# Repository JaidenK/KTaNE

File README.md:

# KTaNE
Keep Talking and Nobody Explodes

# Build Instructions
1. Arduino IDE version 2.2.1
2. Clear out your Arduino libraries folder.
    - ex: "C:\Users\kingj\OneDrive\Documents\Arduino\libraries\" should exist and be empty
3. Copy the contents of the repo's libraries folder into your Arduino install's libraries folder, excluding libraries that do not apply to the desired module.
    - ex: For compiling the Sketchpad module, you would copy ES_Framework, KTaNE, and KTaNE_Sketchpad but NOT KTaNE_Timer or other Module folders
4. Select "Arduino Uno" in the Aruino IDE's board selection menu

The code should now build.

# Programming Instructions
0. Refer to https://docs.arduino.cc/built-in-examples/arduino-isp/ArduinoToBreadboard/
    - See also: https://www.instructables.com/Configure-Arduino-IDE-for-Atmega-328P-to-Use-8MHz-/
    - See also: https://www.youtube.com/watch?v=dcLeKj00t_I
1. Get an Aruino Uno R3 and upload the "ArduinoISP" example sketch to it.
3. Connect the 6-pin ISP header on the Arduino to the 6-pin ISP header on the Module, with the exception of the RESET pin.
4. Connect pin 10 on the Arduino to the Reset pin of the Module's ISP header.
    - Pin 10 is the Arduino's default Slave Select pin for the ArduinoISP sketch.
5. Set the Arduino IDE's programmer to "Arduino as ISP" and select "ATMega328P on a breadboard (8 MHz internal clock)" for the board
6. Use "Sketch > Upload Using Programmer" menu command to upload the code

# Documentation
Communication Protocols:
https://docs.google.com/document/d/1BFYc2orsP6i7TOAGHv1l20GYD-Ui4hXYQUHcmJRFHF8/edit?usp=sharing

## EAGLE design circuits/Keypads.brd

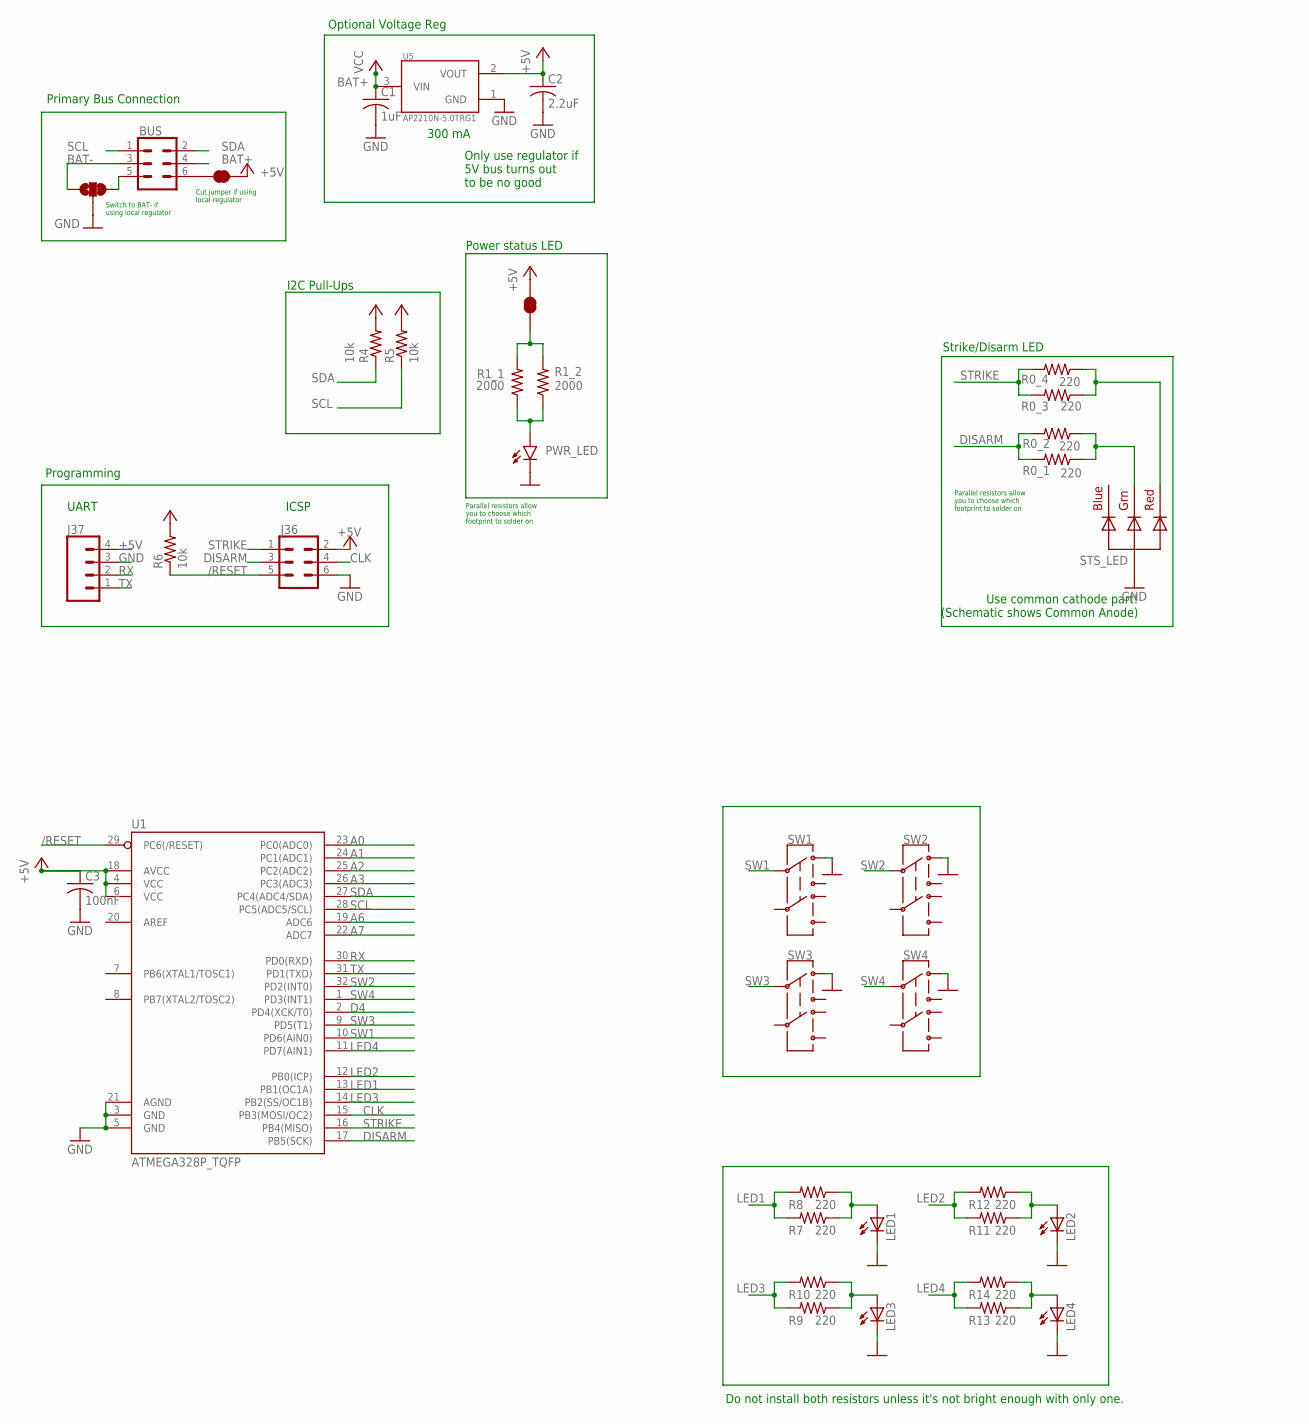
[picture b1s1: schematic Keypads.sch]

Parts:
BUS: CONN_03X2SHROUD; 2X3-SHROUDED
C1: 1uF; C0805
C2: 2.2uF; C0805
C3: 100nF; C0805
J36: CONN_03X22X3_SILK_MALE_PTH; 2X3
J37: CONN_04; 1X04
JP1, JP3: JUMPER-SMT_2_NC_TRACE_SILK; SMT-JUMPER_2_NC_TRACE_SILK
JP2: JUMPER-SMT_3_1-NC_TRACE_SILK; SMT-JUMPER_3_1-NC_TRACE_SILK
LED1, LED2, LED3, LED4: LEDCHIP-LED0603; CHIP-LED0603
PWR_LED: LED3MM; LED_3MM
R0_1, R0_3: 220; 0204/7
R0_2, R0_4, R7, R8, R9, R10, R11, R12, R13, R14: 220; R0805
R1_1: 2000; 0204/7
R1_2: 2000; R0805
R4, R5, R6: 10k; 0204/7
STS_LED: RGBLED_CA-5MM; LED5MMRGB
SW1, SW2, SW3, SW4: MHPS2283N-SWITCH-PUSH-DPDT; MHPS2283N
U1: ATMEGA328P_TQFP; TQFP32-08
U5: AP2210N-5.0TRG1; SOT95P280X145-3N

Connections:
+5V: C2.1, C3.1, J36.2, J37.4, JP1.2, JP3.2, R4.2, R5.2, R6.2, U1.4 (VCC), U1.6 (VCC), U1.18 (AVCC), U5.2 (VOUT)
/RESET: J36.5, R6.1, U1.29 (PC6(/RESET))
A0: U1.23 (PC0(ADC0))
A1: U1.24 (PC1(ADC1))
A2: U1.25 (PC2(ADC2))
A3: U1.26 (PC3(ADC3))
A6: U1.19 (ADC6)
A7: U1.22 (ADC7)
BAT+: BUS.4, C1.1, U5.3 (VIN)
BAT-: BUS.3, JP2.1
CLK: J36.4, U1.15 (PB3(MOSI/OC2))
CONN_5V: BUS.6, JP1.1
CONN_GND: BUS.5, JP2.3
D4: U1.2 (PD4(XCK/T0))
DISARM: J36.3, R0_1.2, R0_2.2, U1.17 (PB5(SCK))
GND: C1.2, C2.2, C3.2, J36.6, J37.3, JP2.2, LED1.C, LED2.C, LED3.C, LED4.C, PWR_LED.K (C), STS_LED.2 (VCC), SW1.P$1 (1), SW2.P$1 (1), SW3.P$1 (1), SW4.P$1 (1), U1.3 (GND), U1.5 (GND), U1.21 (AGND), U5.1 (GND)
LED1: R7.2, R8.2, U1.13 (PB1(OC1A))
LED2: R11.2, R12.2, U1.12 (PB0(ICP))
LED3: R9.2, R10.2, U1.14 (PB2(SS/OC1B))
LED4: R13.2, R14.2, U1.11 (PD7(AIN1))
unnamed: PWR_LED.A, R1_1.1, R1_2.1
unnamed: JP3.1, R1_1.2, R1_2.2
unnamed: LED3.A, R9.1, R10.1
unnamed: LED1.A, R7.1, R8.1
unnamed: LED2.A, R11.1, R12.1
unnamed: LED4.A, R13.1, R14.1
unnamed: R0_1.1, R0_2.1, STS_LED.3 (GREEN)
unnamed: R0_3.1, R0_4.1, STS_LED.1 (RED)
RX: J37.2, U1.30 (PD0(RXD))
SCL: BUS.1, R5.1, U1.28 (PC5(ADC5/SCL))
SDA: BUS.2, R4.1, U1.27 (PC4(ADC4/SDA))
STRIKE: J36.1, R0_3.2, R0_4.2, U1.16 (PB4(MISO))
SW1: SW1.P$2 (2), U1.10 (PD6(AIN0))
SW2: SW2.P$2 (2), U1.32 (PD2(INT0))
SW3: SW3.P$2 (2), U1.9 (PD5(T1))
SW4: SW4.P$2 (2), U1.1 (PD3(INT1))
TX: J37.1, U1.31 (PD1(TXD))

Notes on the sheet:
Only use regulator if 5V bus turns out to be no good
300 mA
Cut jumper if using local regulator
Use common cathode part! (Schematic shows Common Anode)
Switch to BAT- if using local regulator
Power status LED
ICSP
UART
I2C Pull-Ups
Primary Bus Connection
Optional Voltage Reg
Strike/Disarm LED
Programming
Do not install both resistors unless it's not bright enough with only one.
Parallel resistors allow you to choose which footprint to solder on

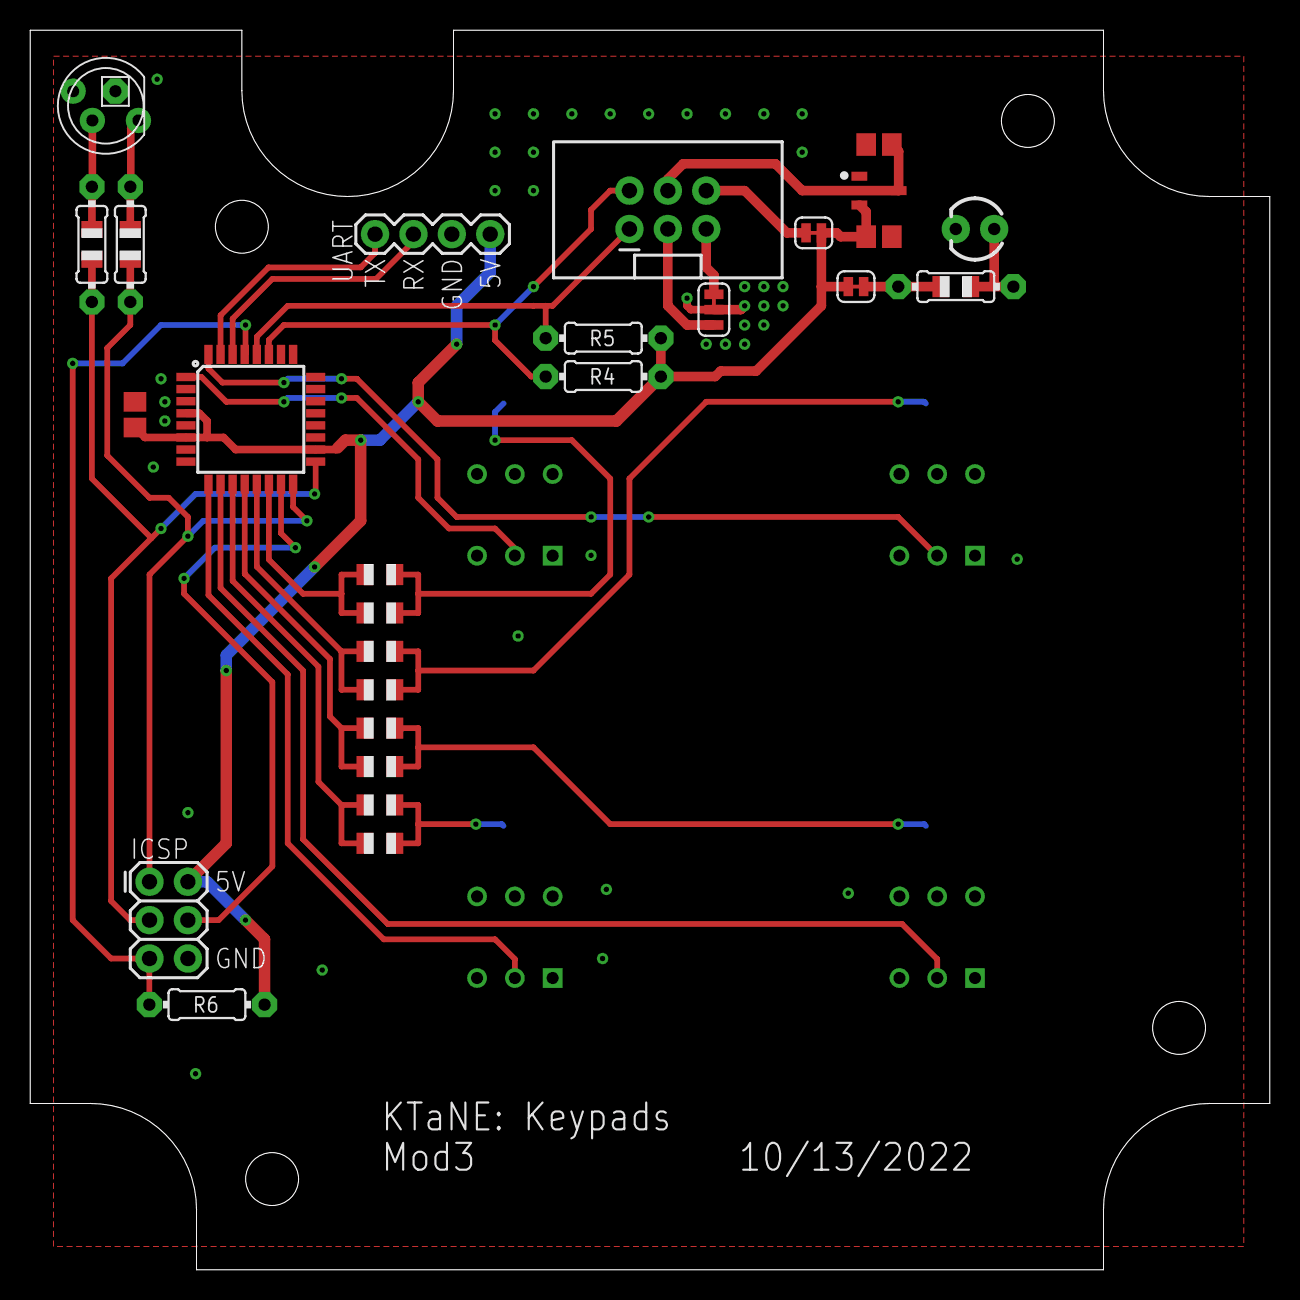
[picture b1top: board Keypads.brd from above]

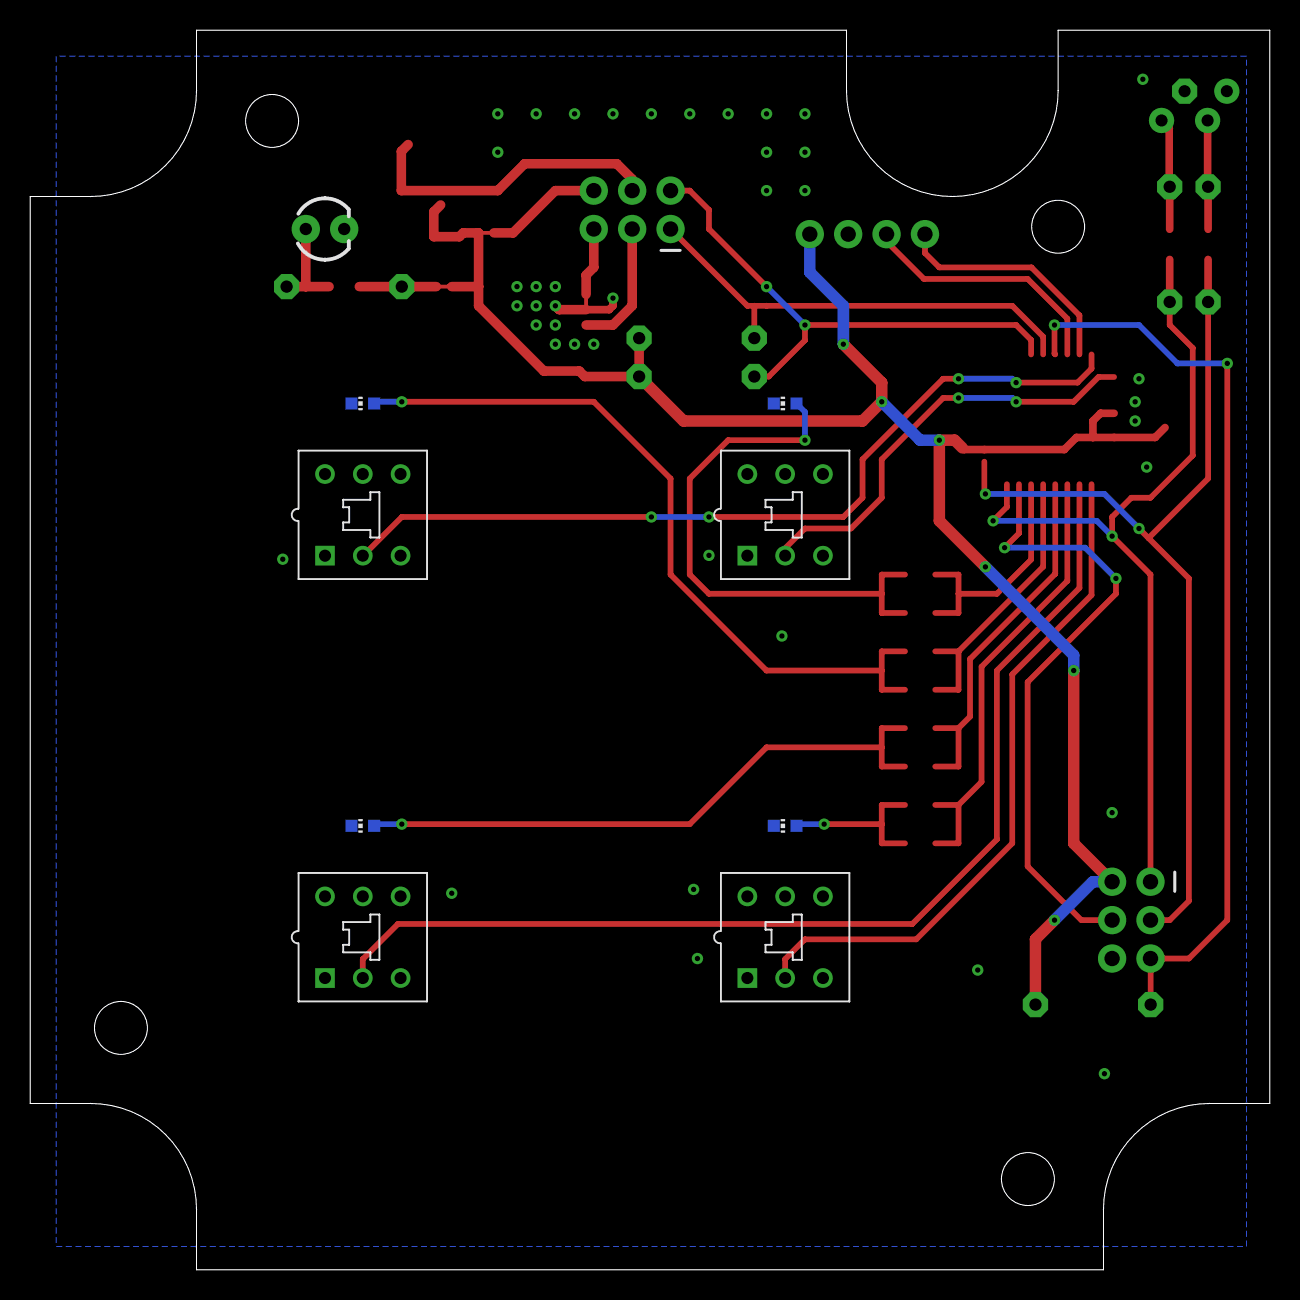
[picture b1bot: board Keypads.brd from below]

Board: 2 copper layers, 82.0 x 82.0 mm, 38 parts (8 on the bottom side), 30 nets.

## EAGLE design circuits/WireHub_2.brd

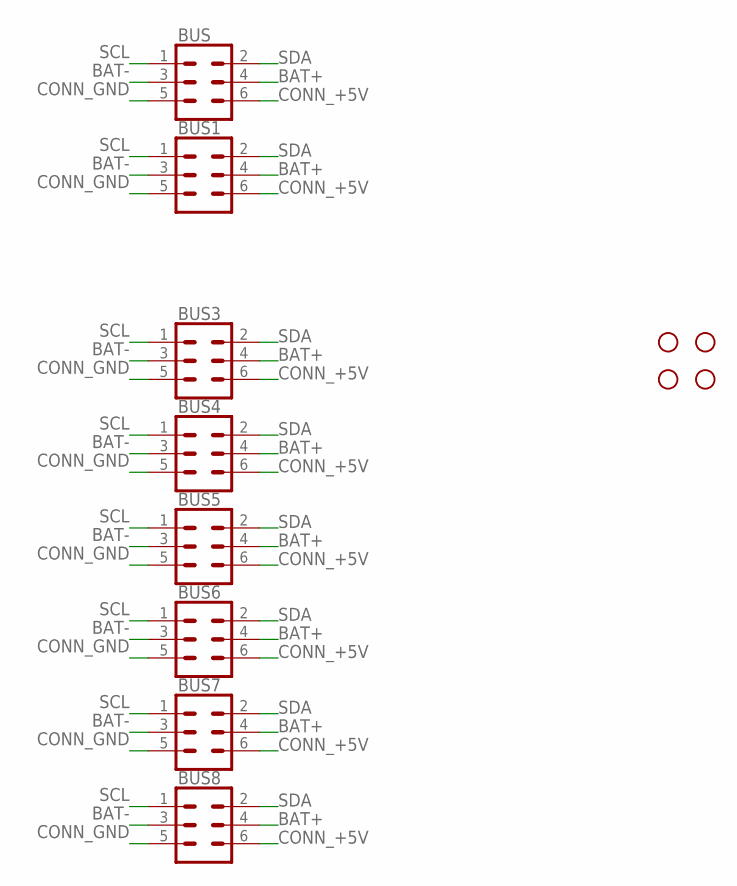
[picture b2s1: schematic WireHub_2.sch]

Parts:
BUS, BUS1, BUS3, BUS4, BUS5, BUS6, BUS7, BUS8: CONN_03X2SHROUD; 2X3-SHROUDED
H1, H2, H3, H4: STAND-OFF

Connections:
BAT+: BUS.4, BUS1.4, BUS3.4, BUS4.4, BUS5.4, BUS6.4, BUS7.4, BUS8.4
BAT-: BUS.3, BUS1.3, BUS3.3, BUS4.3, BUS5.3, BUS6.3, BUS7.3, BUS8.3
CONN_+5V: BUS.6, BUS1.6, BUS3.6, BUS4.6, BUS5.6, BUS6.6, BUS7.6, BUS8.6
CONN_GND: BUS.5, BUS1.5, BUS3.5, BUS4.5, BUS5.5, BUS6.5, BUS7.5, BUS8.5
SCL: BUS.1, BUS1.1, BUS3.1, BUS4.1, BUS5.1, BUS6.1, BUS7.1, BUS8.1
SDA: BUS.2, BUS1.2, BUS3.2, BUS4.2, BUS5.2, BUS6.2, BUS7.2, BUS8.2

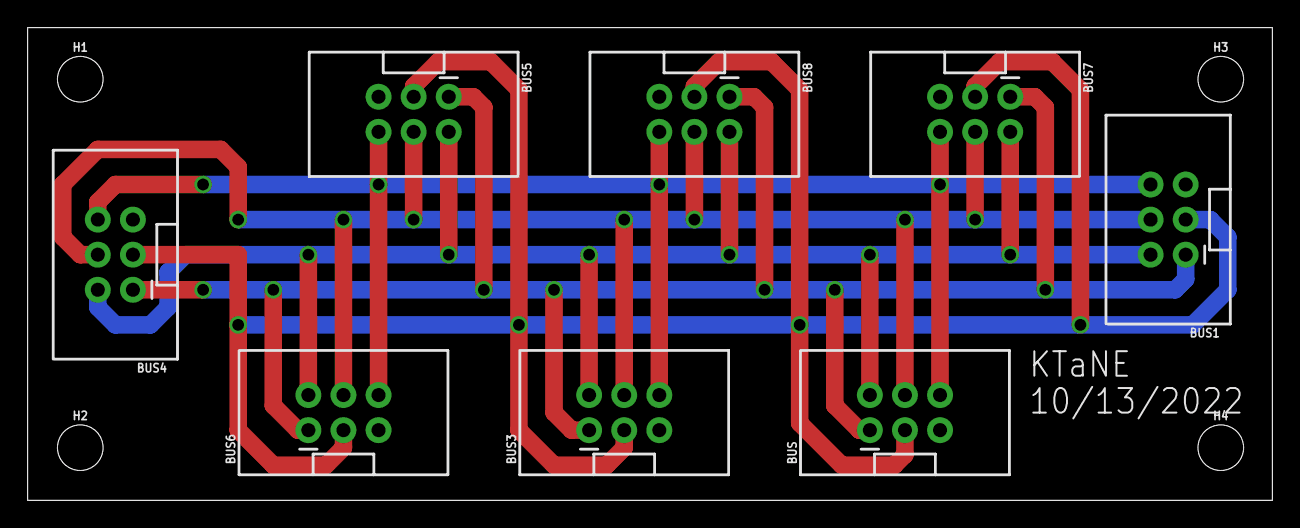
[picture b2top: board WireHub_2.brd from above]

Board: 2 copper layers, 90.1 x 34.2 mm, 12 parts (0 on the bottom side), 6 nets.

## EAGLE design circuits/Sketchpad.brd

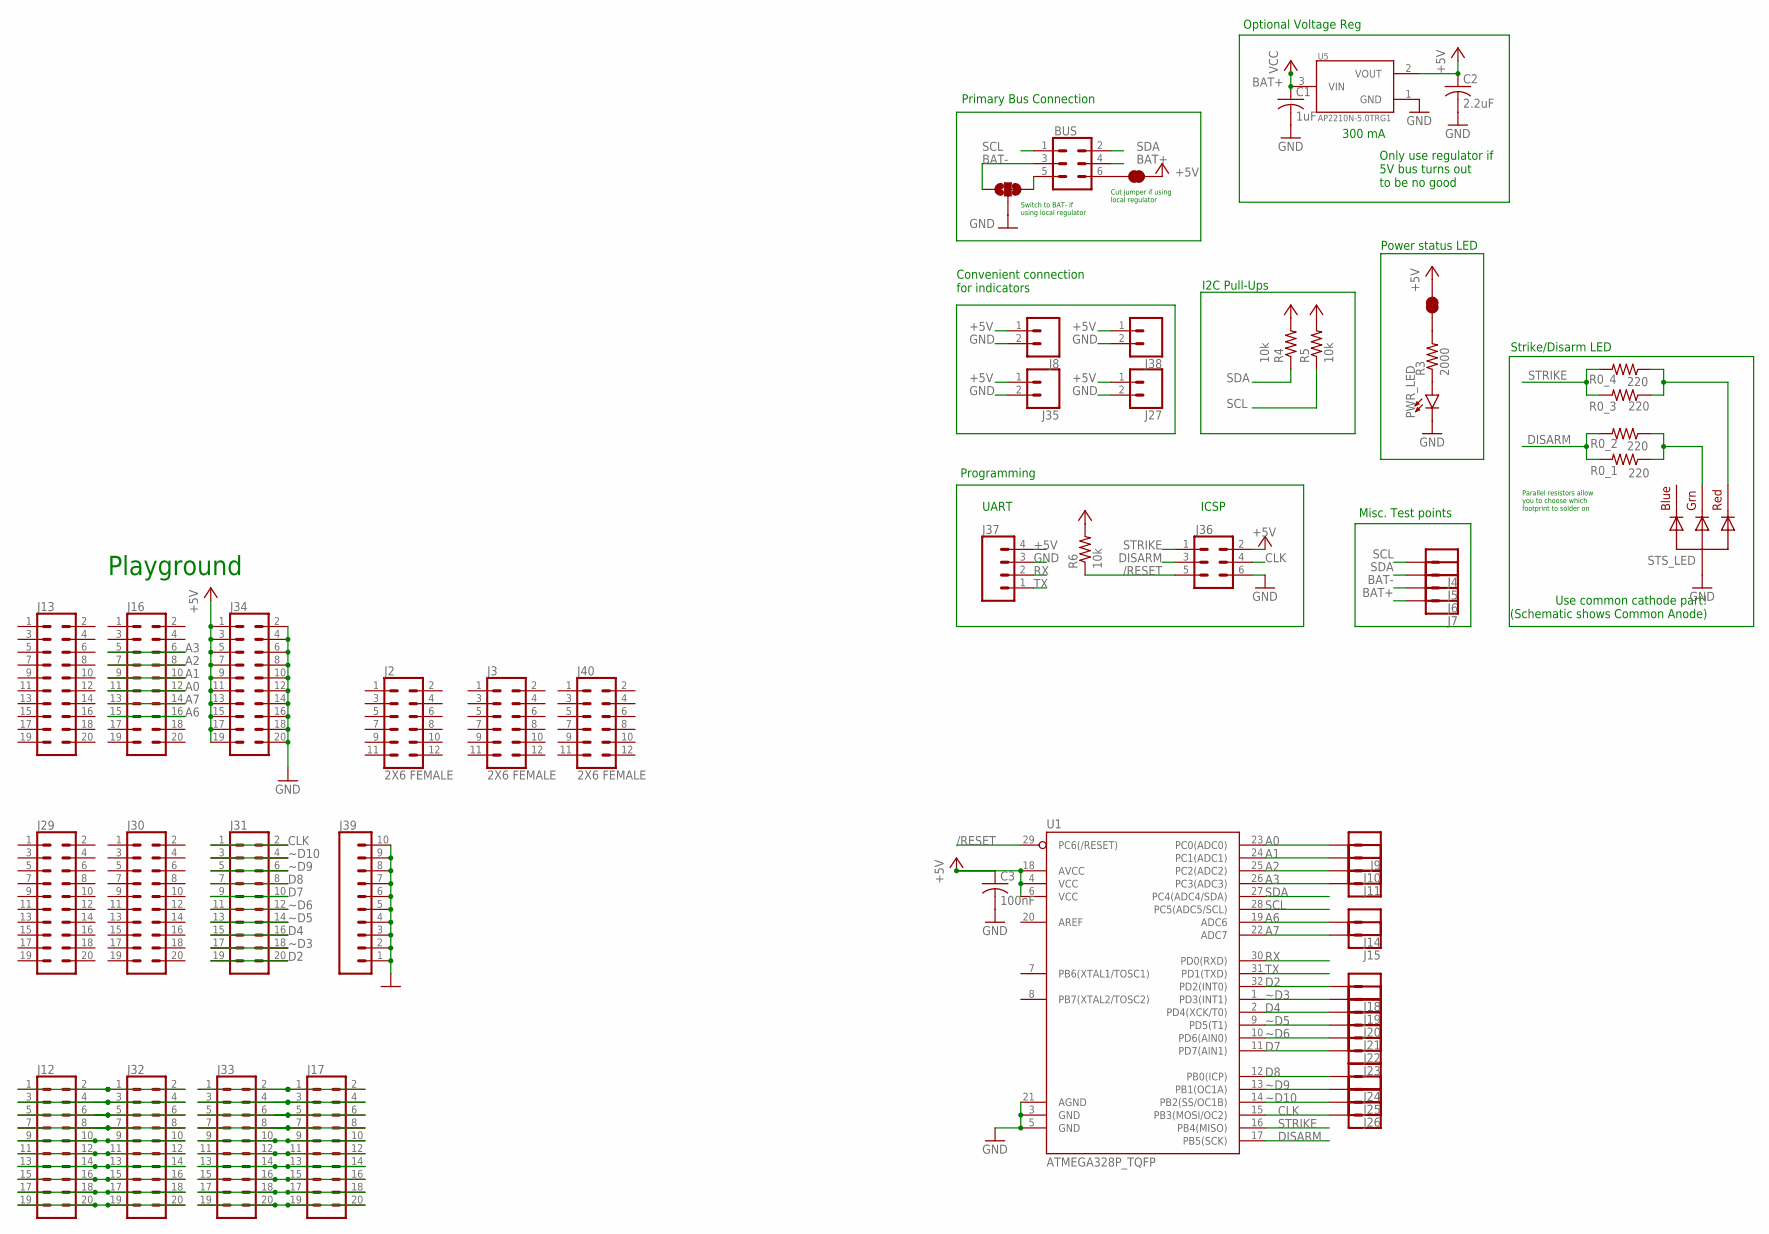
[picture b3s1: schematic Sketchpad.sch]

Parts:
BUS: CONN_03X2SHROUD; 2X3-SHROUDED
C1: 1uF; C0805
C2: 2.2uF; C0805
C3: 100nF; C0805
J1, J4, J5, J6, J7, J9, J10, J11, J14, J15, J18, J19, J20, J21, J22, J23, J24, J25, J26, J28: CONN_01; 1X01
J2, J3, J40: 2X6 FEMALE; 2X6
J8, J27, J35, J38: CONN_02POLAR; MOLEX-1X2
J12, J13, J16, J17, J29, J30, J31, J32, J33, J34: CONN_10X2NOSILK; 2X10_NOSILK
J36: CONN_03X22X3_SILK_MALE_PTH; 2X3
J37: CONN_04; 1X04
J39: CONN_10NO_SILK_PTH_FEMALE; 1X10_NO_SILK
JP1, JP3: JUMPER-SMT_2_NC_TRACE_SILK; SMT-JUMPER_2_NC_TRACE_SILK
JP2: JUMPER-SMT_3_1-NC_TRACE_SILK; SMT-JUMPER_3_1-NC_TRACE_SILK
PWR_LED: LED3MM; LED_3MM
R0_1, R0_3: 220; 0204/7
R0_2, R0_4: 220; R0805
R3: 2000; 0204/7
R4, R5, R6: 10k; 0204/7
STS_LED: RGBLED_CA-5MM; LED5MMRGB
U1: ATMEGA328P_TQFP; TQFP32-08
U5: AP2210N-5.0TRG1; SOT95P280X145-3N

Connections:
+5V: C2.1, C3.1, J8.1, J27.1, J34.1, J34.3, J34.5, J34.7, J34.9, J34.11, J34.13, J34.15, J34.17, J34.19, J35.1, J36.2, J37.4, J38.1, JP1.2, JP3.2, R4.2, R5.2, R6.2, U1.4 (VCC), U1.6 (VCC), U1.18 (AVCC), U5.2 (VOUT)
/RESET: J36.5, R6.1, U1.29 (PC6(/RESET))
A0: J9.1, J16.11, J16.12, U1.23 (PC0(ADC0))
A1: J10.1, J16.9, J16.10, U1.24 (PC1(ADC1))
A2: J11.1, J16.7, J16.8, U1.25 (PC2(ADC2))
A3: J16.5, J16.6, J28.1, U1.26 (PC3(ADC3))
A6: J14.1, J16.15, J16.16, U1.19 (ADC6)
A7: J15.1, J16.13, J16.14, U1.22 (ADC7)
BAT+: BUS.4, C1.1, J7.1, U5.3 (VIN)
BAT-: BUS.3, J6.1, JP2.1
CLK: J1.1, J31.1, J31.2, J36.4, U1.15 (PB3(MOSI/OC2))
CONN_5V: BUS.6, JP1.1
CONN_GND: BUS.5, JP2.3
D2: J18.1, J31.19, J31.20, U1.32 (PD2(INT0))
D4: J20.1, J31.15, J31.16, U1.2 (PD4(XCK/T0))
D7: J23.1, J31.9, J31.10, U1.11 (PD7(AIN1))
D8: J24.1, J31.7, J31.8, U1.12 (PB0(ICP))
DISARM: J36.3, R0_1.2, R0_2.2, U1.17 (PB5(SCK))
GND: C1.2, C2.2, C3.2, J8.2, J27.2, J34.2, J34.4, J34.6, J34.8, J34.10, J34.12, J34.14, J34.16, J34.18, J34.20, J35.2, J36.6, J37.3, J38.2, J39.1, J39.2, J39.3, J39.4, J39.5, J39.6, J39.7, J39.8, J39.9, J39.10, JP2.2, PWR_LED.K (C), STS_LED.2 (VCC), U1.3 (GND), U1.5 (GND), U1.21 (AGND), U5.1 (GND)
unnamed: R0_1.1, R0_2.1, STS_LED.3 (GREEN)
unnamed: R0_3.1, R0_4.1, STS_LED.1 (RED)
unnamed: J12.1, J12.2, J32.1, J32.2
unnamed: J12.3, J12.4, J32.3, J32.4
unnamed: J12.5, J12.6, J32.5, J32.6
unnamed: J12.7, J12.8, J32.7, J32.8
unnamed: J12.9, J12.10, J32.9, J32.10
unnamed: J12.11, J12.12, J32.11, J32.12
unnamed: J12.13, J12.14, J32.13, J32.14
unnamed: J12.15, J12.16, J32.15, J32.16
unnamed: J12.17, J12.18, J32.17, J32.18
unnamed: J12.19, J12.20, J32.19, J32.20
unnamed: J17.1, J17.2, J33.1, J33.2
unnamed: J17.3, J17.4, J33.3, J33.4
unnamed: J17.5, J17.6, J33.5, J33.6
unnamed: J17.7, J17.8, J33.7, J33.8
unnamed: J17.9, J17.10, J33.9, J33.10
unnamed: J17.11, J17.12, J33.11, J33.12
unnamed: J17.13, J17.14, J33.13, J33.14
unnamed: J17.15, J17.16, J33.15, J33.16
unnamed: J17.17, J17.18, J33.17, J33.18
unnamed: J17.19, J17.20, J33.19, J33.20
unnamed: JP3.1, R3.2
unnamed: PWR_LED.A, R3.1
RX: J37.2, U1.30 (PD0(RXD))
SCL: BUS.1, J4.1, R5.1, U1.28 (PC5(ADC5/SCL))
SDA: BUS.2, J5.1, R4.1, U1.27 (PC4(ADC4/SDA))
STRIKE: J36.1, R0_3.2, R0_4.2, U1.16 (PB4(MISO))
TX: J37.1, U1.31 (PD1(TXD))
~D3: J19.1, J31.17, J31.18, U1.1 (PD3(INT1))
~D5: J21.1, J31.13, J31.14, U1.9 (PD5(T1))
~D6: J22.1, J31.11, J31.12, U1.10 (PD6(AIN0))
~D9: J25.1, J31.5, J31.6, U1.13 (PB1(OC1A))
~D10: J26.1, J31.3, J31.4, U1.14 (PB2(SS/OC1B))

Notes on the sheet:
Only use regulator if 5V bus turns out to be no good
300 mA
Cut jumper if using local regulator
Use common cathode part! (Schematic shows Common Anode)
Switch to BAT- if using local regulator
Playground
Misc. Test points
Convenient connection for indicators
Power status LED
ICSP
UART
I2C Pull-Ups
Primary Bus Connection
Optional Voltage Reg
Strike/Disarm LED
Programming
Parallel resistors allow you to choose which footprint to solder on

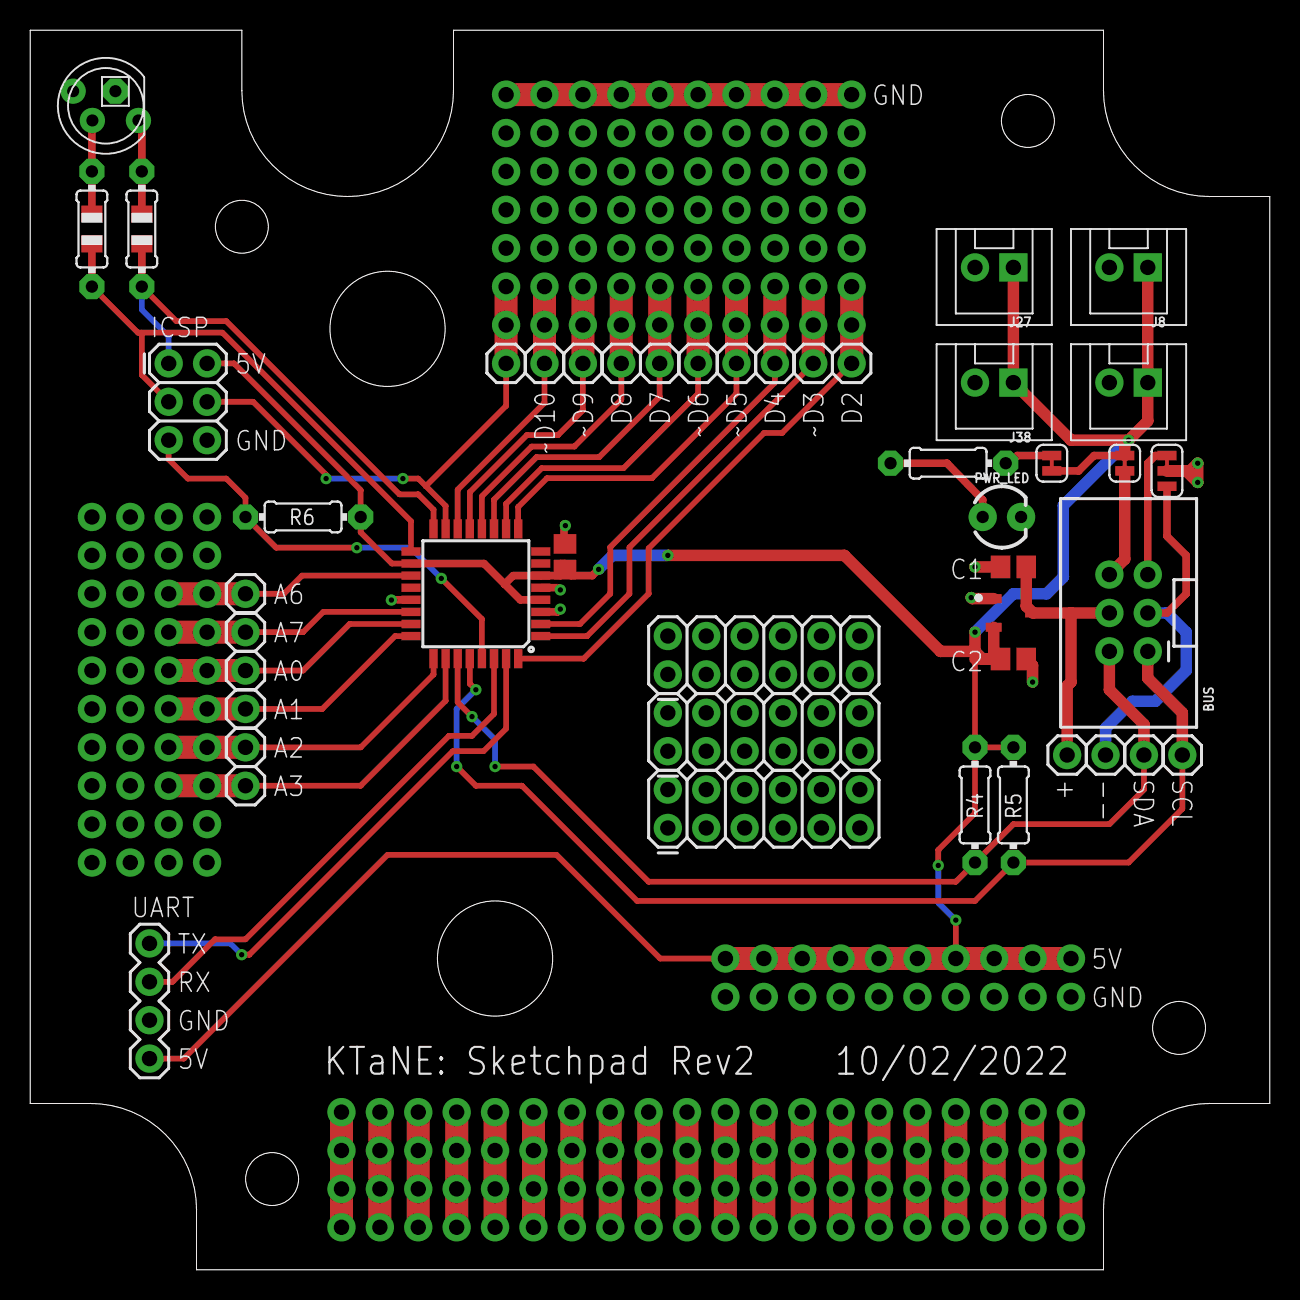
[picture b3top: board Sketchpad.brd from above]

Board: 2 copper layers, 82.0 x 82.0 mm, 59 parts (0 on the bottom side), 53 nets.

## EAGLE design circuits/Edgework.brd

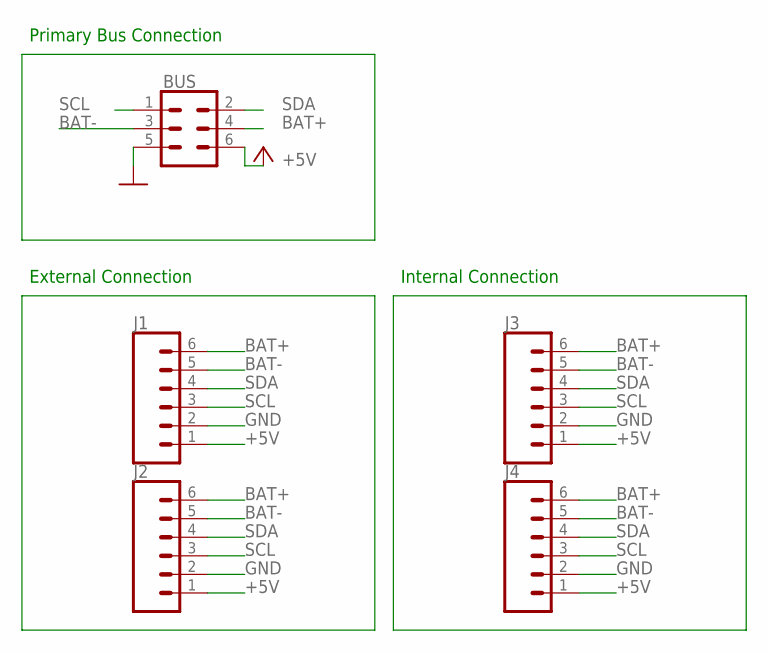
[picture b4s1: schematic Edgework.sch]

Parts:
BUS: CONN_03X2SHROUD; 2X3-SHROUDED
J1, J2, J3, J4: CONN_06NO_SILK_FEMALE_PTH; 1X06_NO_SILK

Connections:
+5V: BUS.6, J1.1, J2.1, J3.1, J4.1
BAT+: BUS.4, J1.6, J2.6, J3.6, J4.6
BAT-: BUS.3, J1.5, J2.5, J3.5, J4.5
GND: BUS.5, J1.2, J2.2, J3.2, J4.2
SCL: BUS.1, J1.3, J2.3, J3.3, J4.3
SDA: BUS.2, J1.4, J2.4, J3.4, J4.4

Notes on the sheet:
Primary Bus Connection
External Connection
Internal Connection

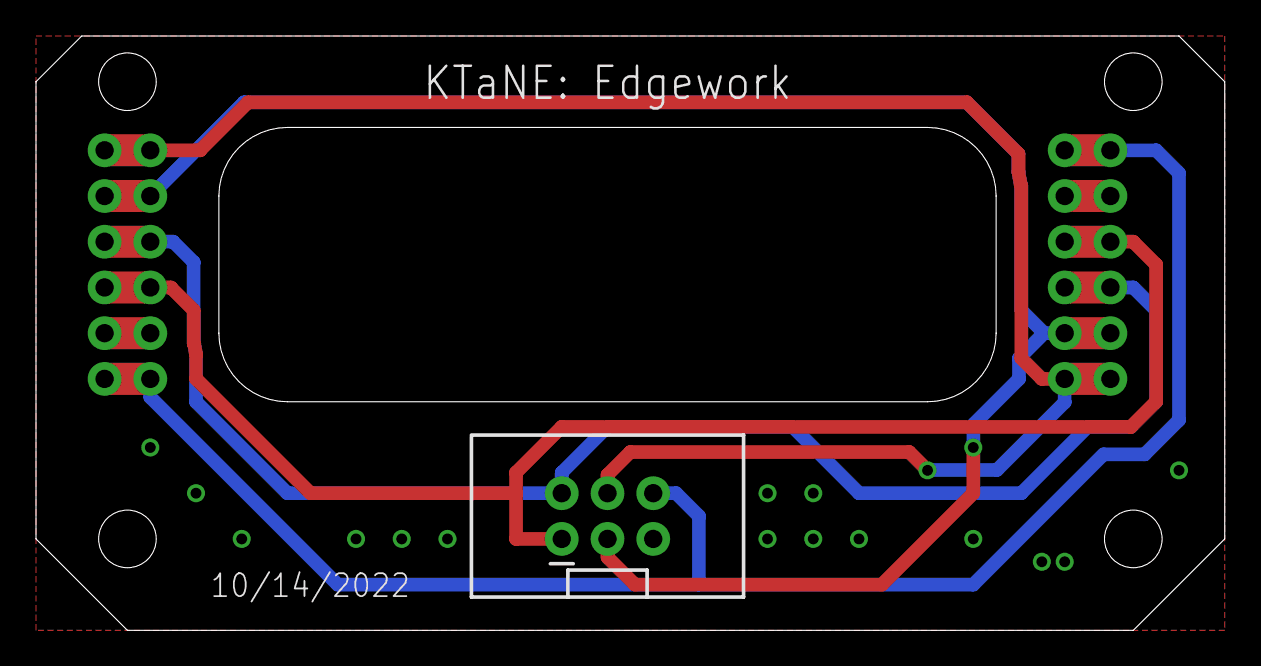
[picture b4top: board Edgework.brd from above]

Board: 2 copper layers, 66.0 x 33.0 mm, 5 parts (0 on the bottom side), 6 nets.

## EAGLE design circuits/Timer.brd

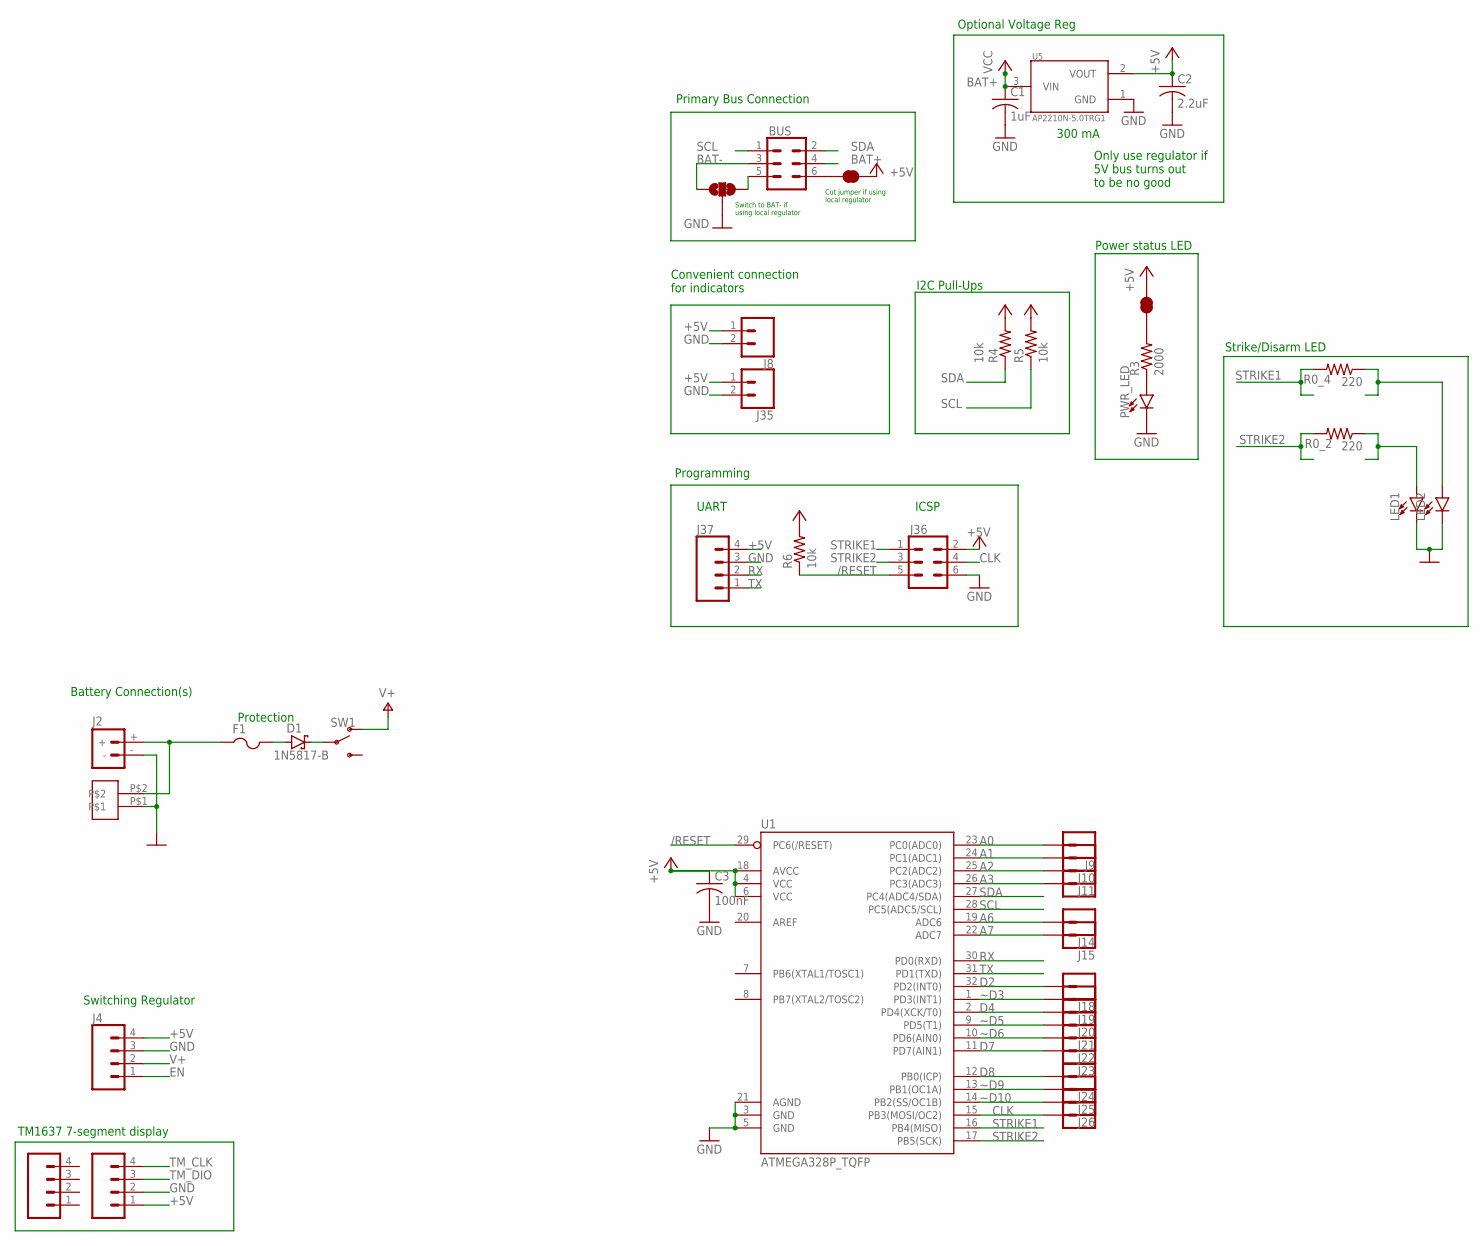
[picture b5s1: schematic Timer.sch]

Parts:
BUS: CONN_03X2SHROUD; 2X3-SHROUDED
C1: 1uF; C0805
C2: 2.2uF; C0805
C3: 100nF; C0805
D1: 1N5817-B; DO41-7.6
F1: FUSE
J1, J9, J10, J11, J14, J15, J18, J19, J20, J21, J22, J23, J24, J25, J26, J28: CONN_01; 1X01
J2: BATTERY_CONN_DEANS; DEANS
J3: ONSHORE_OSTTG025100B
J4, J5, J6: CONN_041X04_NO_SILK; 1X04_NO_SILK
J8, J35: CONN_02POLAR; MOLEX-1X2
J36: CONN_03X22X3_SILK_MALE_PTH; 2X3
J37: CONN_04; 1X04
JP1, JP3: JUMPER-SMT_2_NC_TRACE_SILK; SMT-JUMPER_2_NC_TRACE_SILK
JP2: JUMPER-SMT_3_1-NC_TRACE_SILK; SMT-JUMPER_3_1-NC_TRACE_SILK
LED1, LED2: LED5MM; LED_5MM
PWR_LED: LED0603; LED-0603
R0_2, R0_4: 220; R0805
R3: 2000; R0805
R4, R5: 10k; R0805
R6: 10k; 0204/7
SW1: SLIDE_SWITCH
U1: ATMEGA328P_TQFP; TQFP32-08
U5: AP2210N-5.0TRG1; SOT95P280X145-3N

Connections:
+5V: C2.1, C3.1, J4.4, J5.1, J8.1, J35.1, J36.2, J37.4, JP1.2, JP3.2, R4.2, R5.2, R6.2, U1.4 (VCC), U1.6 (VCC), U1.18 (AVCC), U5.2 (VOUT)
/RESET: J36.5, R6.1, U1.29 (PC6(/RESET))
A0: J9.1, U1.23 (PC0(ADC0))
A1: J10.1, U1.24 (PC1(ADC1))
A2: J11.1, U1.25 (PC2(ADC2))
A3: J28.1, U1.26 (PC3(ADC3))
A6: J14.1, U1.19 (ADC6)
A7: J15.1, U1.22 (ADC7)
BAT+: BUS.4, C1.1, U5.3 (VIN)
BAT-: BUS.3, JP2.1
BATT_DIRECT: F1.P$1 (1), F1.P$2 (1), J2.+, J3.P$2
CLK: J1.1, J36.4, U1.15 (PB3(MOSI/OC2))
CONN_5V: BUS.6, JP1.1
CONN_GND: BUS.5, JP2.3
D2: J18.1, U1.32 (PD2(INT0))
D4: J20.1, U1.2 (PD4(XCK/T0))
D7: J23.1, U1.11 (PD7(AIN1))
D8: J24.1, U1.12 (PB0(ICP))
DBAT: D1.C, SW1.P$2
EN: J4.1
GND: C1.2, C2.2, C3.2, J2.-, J3.P$1, J4.3, J5.2, J8.2, J35.2, J36.6, J37.3, JP2.2, LED1.K (C), LED2.K (C), PWR_LED.C, U1.3 (GND), U1.5 (GND), U1.21 (AGND), U5.1 (GND)
unnamed: LED1.A, R0_2.1
unnamed: LED2.A, R0_4.1
unnamed: D1.A, F1.P$3 (2), F1.P$4 (2)
unnamed: JP3.1, R3.2
unnamed: PWR_LED.A, R3.1
RX: J37.2, U1.30 (PD0(RXD))
SCL: BUS.1, R5.1, U1.28 (PC5(ADC5/SCL))
SDA: BUS.2, R4.1, U1.27 (PC4(ADC4/SDA))
STRIKE1: J36.1, R0_4.2, U1.16 (PB4(MISO))
STRIKE2: J36.3, R0_2.2, U1.17 (PB5(SCK))
TM_CLK: J5.4
TM_DIO: J5.3
TX: J37.1, U1.31 (PD1(TXD))
V+: J4.2, SW1.P$1 (O)
~D3: J19.1, U1.1 (PD3(INT1))
~D5: J21.1, U1.9 (PD5(T1))
~D6: J22.1, U1.10 (PD6(AIN0))
~D9: J25.1, U1.13 (PB1(OC1A))
~D10: J26.1, U1.14 (PB2(SS/OC1B))

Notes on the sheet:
Only use regulator if 5V bus turns out to be no good
300 mA
Cut jumper if using local regulator
Switch to BAT- if using local regulator
Convenient connection for indicators
Power status LED
ICSP
UART
I2C Pull-Ups
Primary Bus Connection
Optional Voltage Reg
Strike/Disarm LED
Battery Connection(s)
Programming
Protection
Switching Regulator
TM1637 7-segment display

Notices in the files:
parts and their libraries:
SparkFun-Connectors: Licensing: Creative Commons ShareAlike 4.0 International - https://creativecommons.org/licenses/by-sa/4.0
